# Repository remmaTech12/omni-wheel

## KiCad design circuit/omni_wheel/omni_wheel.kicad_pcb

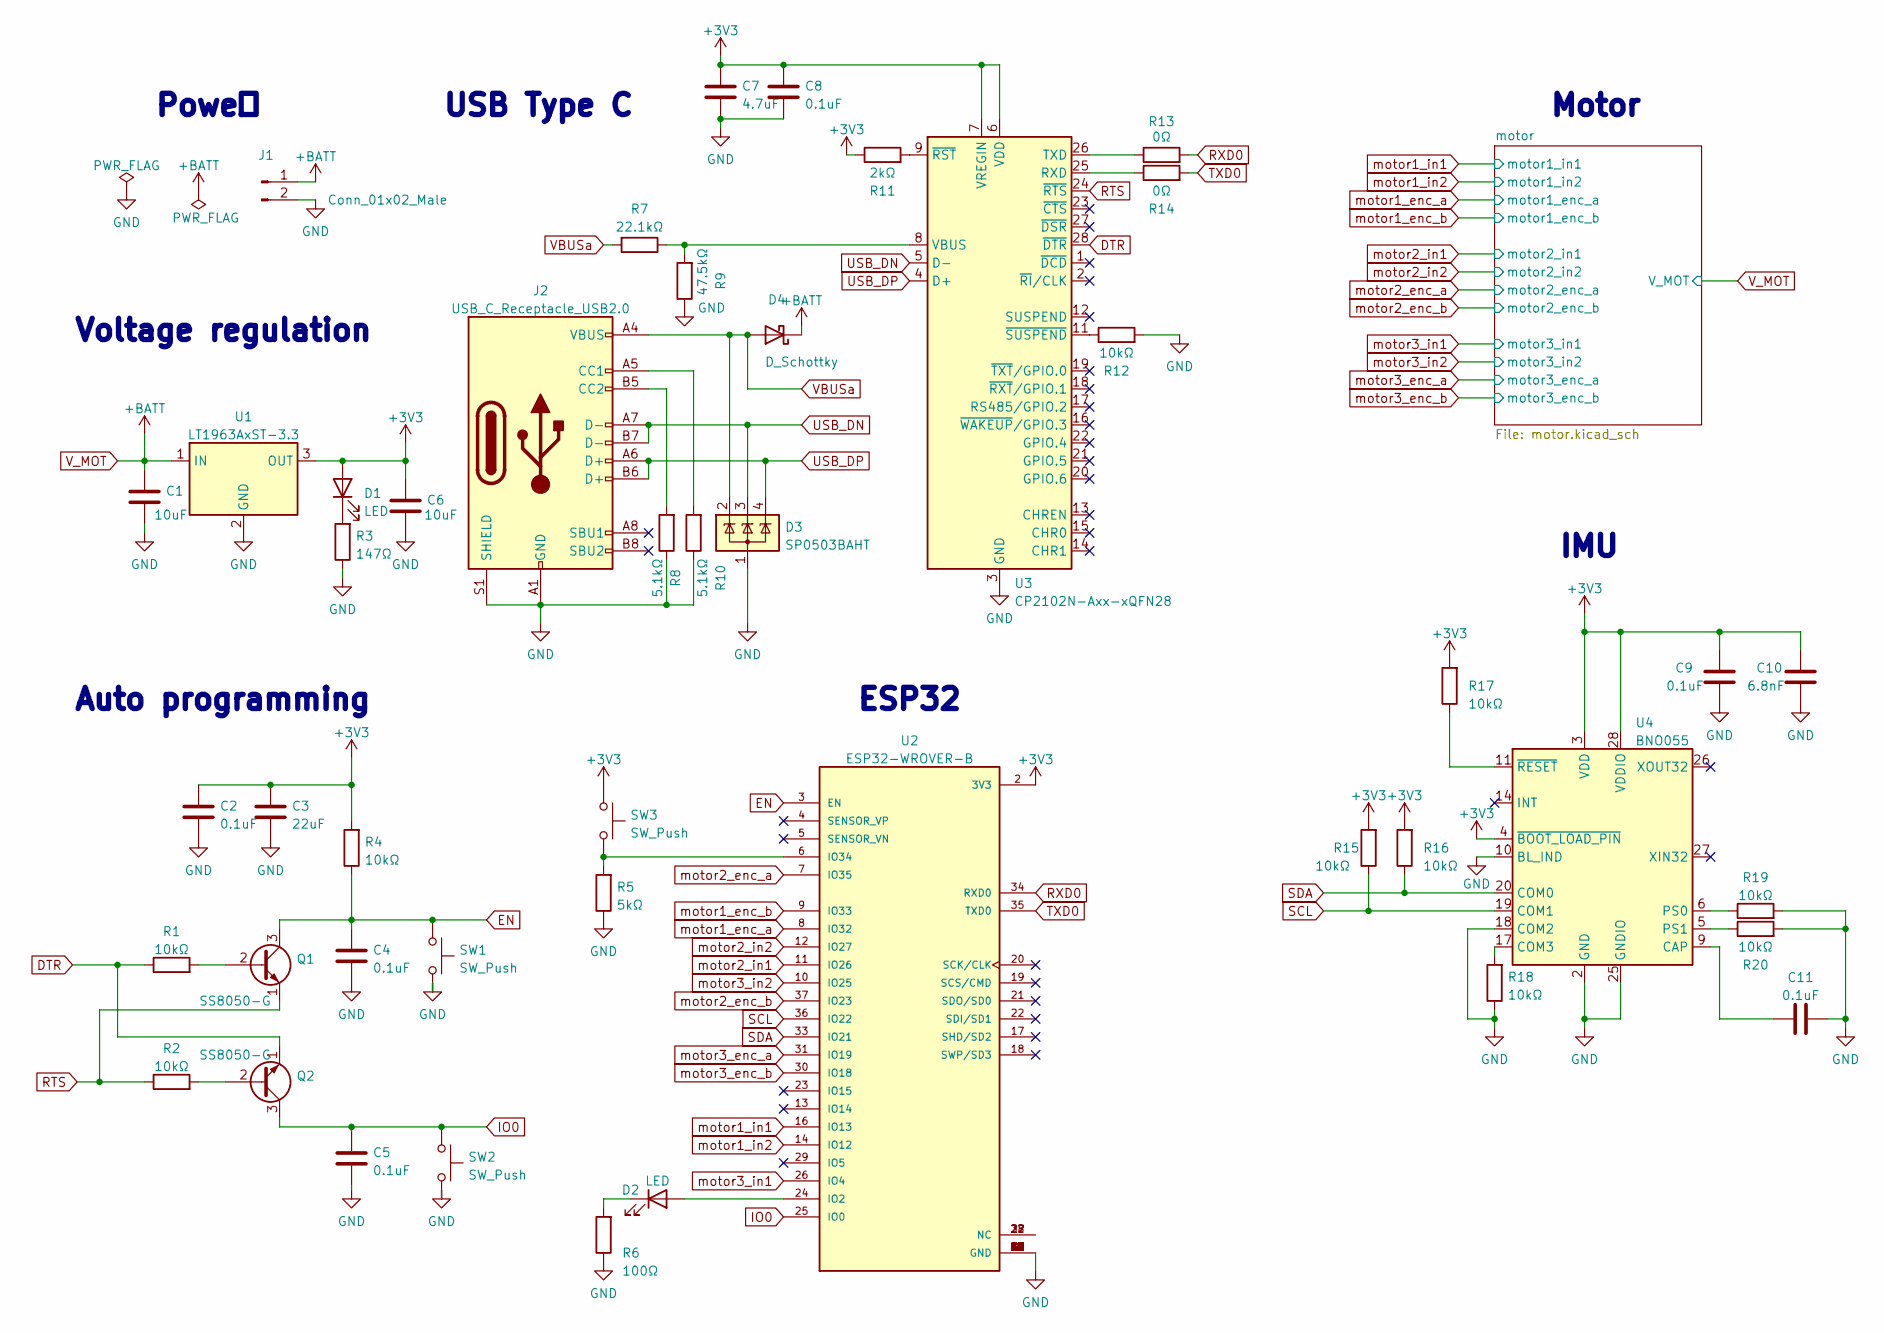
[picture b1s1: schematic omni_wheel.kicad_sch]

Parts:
C1, C6: 10uF; C_0603_1608Metric
C2, C4, C5, C8, C9, C11: 0.1uF; C_0603_1608Metric
C3: 22uF; C_0603_1608Metric
C7: 4.7uF; C_0603_1608Metric
C10: 6.8nF; C_0603_1608Metric
D1, D2: LED; D_0603_1608Metric
D3: SP0503BAHT; SOT-143
D4: D_Schottky; D_0603_1608Metric
J1: Conn_01x02_Male; PinSocket_1x02_P2.54mm_Vertical
J2: USB_C_Receptacle_USB2.0; USB_C_Receptacle_Amphenol_12401610E4-2A
Q1, Q2: SS8050-G; SOT-23
R1, R2, R4, R12, R15, R16, R17, R18, R19, R20: 10kΩ; R_0603_1608Metric
R3: 147Ω; R_0603_1608Metric
R5: 5kΩ; R_0603_1608Metric
R6: 100Ω; R_0603_1608Metric
R7: 22.1kΩ; R_0603_1608Metric
R8, R10: 5.1kΩ; R_0603_1608Metric
R9: 47.5kΩ; R_0603_1608Metric
R11: 2kΩ; R_0603_1608Metric
R13, R14: 0Ω; R_0603_1608Metric
SW1, SW2: SW_Push; SW_Push_1P1T_NO_CK_KMR2
SW3: SW_Push; SW_Push_1P1T_NO_6x6mm_H9.5mm
U1: LT1963AxST-3.3; SOT-223-3_TabPin2
U2: ESP32-WROVER-B; MODULE_ESP32-WROVER-B; PARTREV v1.6
U3: CP2102N-Axx-xQFN28; QFN-28-1EP_5x5mm_P0.5mm_EP3.35x3.35mm
U4: BNO055; LGA-28_5.2x3.8mm_P0.5mm

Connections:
+3V3: C2.1, C3.1, C6.1, C7.1, C8.1, C9.2, C10.2, D1.2 (A), R4.2, R11.1, R15.2, R16.2, R17.2, SW3.1, U1.3 (OUT), U2.2 (3V3), U3.6 (VDD), U3.7 (VREGIN), U4.3 (VDD), U4.4 (~BOOT_LOAD_PIN), U4.28 (VDDIO); also elsewhere on the board
DTR: Q2.1 (E), R1.1, U3.28 (~DTR)
EN: C4.1, Q1.3 (C), R4.1, SW1.1, U2.3 (EN)
GND: C1.2, C2.2, C3.2, C4.2, C5.2, C6.2, C7.2, C8.2, C9.1, C10.1, C11.2, D3.1 (A), J1.2, J2.A1 (GND), J2.A12 (GND), J2.B1 (GND), J2.B12 (GND), J2.S1 (SHIELD), R3.1, R5.1, R6.1, R8.1, R9.1, R10.1, R12.2, R18.1, R19.2, R20.2, SW1.2, SW2.2, U1.2 (GND), U2.1 (GND), U2.15 (GND), U2.38 (GND), U2.39 (GND), U2.40 (GND), U2.41 (GND), U2.42 (GND), U2.43 (GND), U2.44 (GND), U2.45 (GND), U2.46 (GND), U2.47 (GND), U2.48 (GND), U2.49 (GND), U2.50 (GND), U2.51 (GND), U2.52 (GND), U2.53 (GND), U2.54 (GND), U2.55 (GND), U2.56 (GND), U2.57 (GND), U2.58 (GND), U2.59 (GND), U3.3 (GND), U3.29 (GND), U4.2 (GND), U4.10 (BL_IND), U4.15 (GNDIO), U4.16 (GNDIO), U4.18 (COM2), U4.25 (GNDIO); also elsewhere on the board
IO0: C5.1, Q2.3 (C), SW2.1, U2.25 (IO0)
unnamed: C11.1, U4.9 (CAP)
unnamed: D1.1 (K), R3.2
unnamed: D2.1 (K), R6.2
unnamed: D2.2 (A), U2.24 (IO2)
unnamed: J2.A5 (CC1), R10.2
unnamed: J2.B5 (CC2), R8.2
unnamed: Q1.2 (B), R1.2
unnamed: Q2.2 (B), R2.2
unnamed: R5.2, SW3.2, U2.6 (IO34)
unnamed: R7.1, R9.2, U3.8 (VBUS)
unnamed: R11.2, U3.9 (~RST)
unnamed: R12.1, U3.11 (~SUSPEND)
unnamed: R13.1, U3.26 (TXD)
unnamed: R14.1, U3.25 (RXD)
unnamed: R17.1, U4.11 (~RESET)
unnamed: R18.2, U4.17 (COM3)
unnamed: R19.1, U4.6 (PS0)
unnamed: R20.1, U4.5 (PS1)
unnamed: U2.27 (NC), U2.28 (NC), U2.32 (NC)
RTS: Q1.1 (E), R2.1, U3.24 (~RTS)
RXD0: R13.2, U2.34 (RXD0)
SCL: R15.1, U2.36 (IO22), U4.19 (COM1)
SDA: R16.1, U2.33 (IO21), U4.20 (COM0)
TXD0: R14.2, U2.35 (TXD0)
USB_DN: D3.3 (K), J2.A7 (D-), J2.B7 (D-), U3.5 (D-)
USB_DP: D3.4 (K), J2.A6 (D+), J2.B6 (D+), U3.4 (D+)
VBUSa: D3.2 (K), D4.2 (A), J2.A4 (VBUS), J2.A9 (VBUS), J2.B4 (VBUS), J2.B9 (VBUS), R7.2
V_MOT: C1.1, D4.1 (K), J1.1, U1.1 (IN); also elsewhere on the board
motor1_enc_a: U2.8 (IO32); also elsewhere on the board
motor1_enc_b: U2.9 (IO33); also elsewhere on the board
motor1_in1: U2.16 (IO13); also elsewhere on the board
motor1_in2: U2.14 (IO12); also elsewhere on the board
motor2_enc_a: U2.7 (IO35); also elsewhere on the board
motor2_enc_b: U2.37 (IO23); also elsewhere on the board
motor2_in1: U2.11 (IO26); also elsewhere on the board
motor2_in2: U2.12 (IO27); also elsewhere on the board
motor3_enc_a: U2.31 (IO19); also elsewhere on the board
motor3_enc_b: U2.30 (IO18); also elsewhere on the board
motor3_in1: U2.26 (IO4); also elsewhere on the board
motor3_in2: U2.10 (IO25); also elsewhere on the board

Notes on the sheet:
Motor
Poweｒ
Auto programming
IMU
USB Type C
Voltage regulation
ESP32

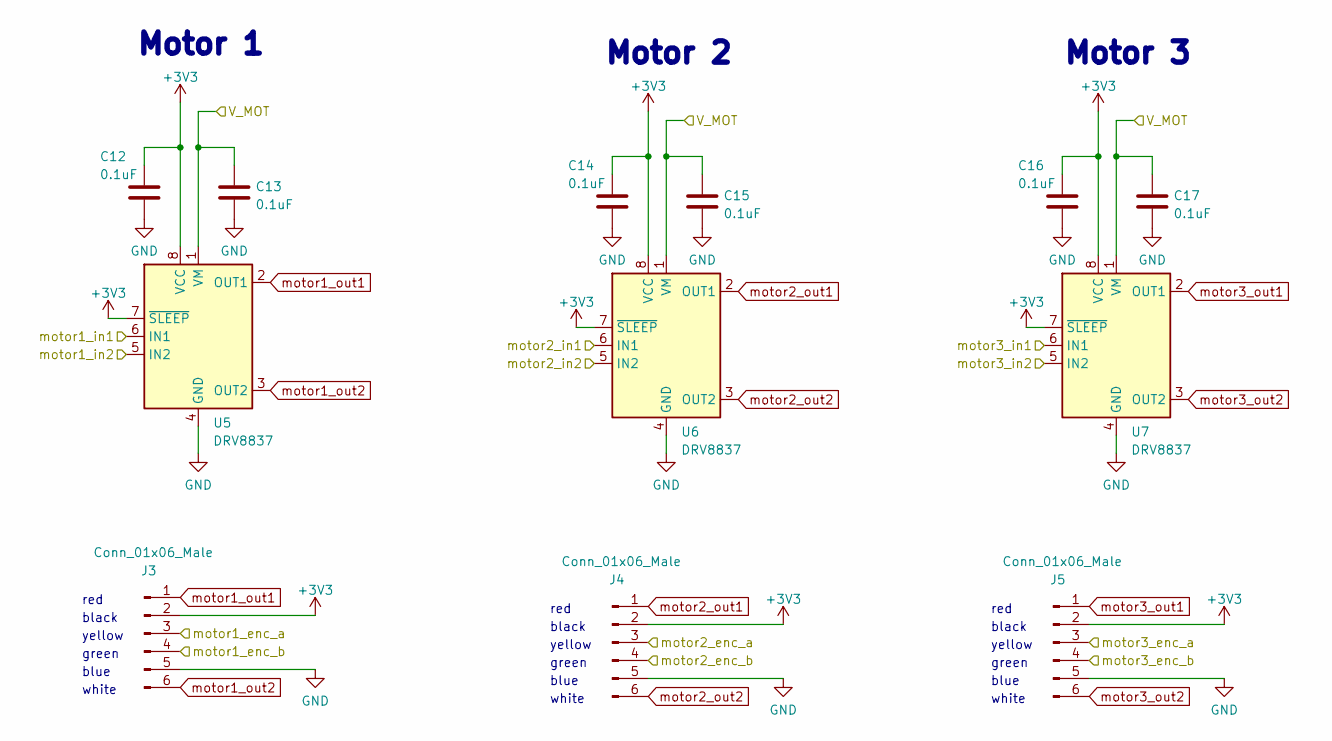
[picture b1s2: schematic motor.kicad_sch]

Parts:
C12, C13, C14, C15, C16, C17: 0.1uF; C_0603_1608Metric
J3, J4, J5: Conn_01x06_Male; PinHeader_1x06_P2.54mm_Vertical
U5, U6, U7: DRV8837; WSON-8-1EP_2x2mm_P0.5mm_EP0.9x1.6mm

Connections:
+3V3: C12.1, C14.1, C16.1, J3.2, J4.2, J5.2, U5.7 (~SLEEP), U5.8 (VCC), U6.7 (~SLEEP), U6.8 (VCC), U7.7 (~SLEEP), U7.8 (VCC); also elsewhere on the board
GND: C12.2, C13.2, C14.2, C15.2, C16.2, C17.2, J3.5, J4.5, J5.5, U5.4 (GND), U5.9 (GND), U6.4 (GND), U6.9 (GND), U7.4 (GND), U7.9 (GND); also elsewhere on the board
V_MOT: C13.1, C15.1, C17.1, U5.1 (VM), U6.1 (VM), U7.1 (VM); also elsewhere on the board
motor1_enc_a: J3.3; also elsewhere on the board
motor1_enc_b: J3.4; also elsewhere on the board
motor1_in1: U5.6 (IN1); also elsewhere on the board
motor1_in2: U5.5 (IN2); also elsewhere on the board
motor1_out1: J3.1, U5.2 (OUT1)
motor1_out2: J3.6, U5.3 (OUT2)
motor2_enc_a: J4.3; also elsewhere on the board
motor2_enc_b: J4.4; also elsewhere on the board
motor2_in1: U6.6 (IN1); also elsewhere on the board
motor2_in2: U6.5 (IN2); also elsewhere on the board
motor2_out1: J4.1, U6.2 (OUT1)
motor2_out2: J4.6, U6.3 (OUT2)
motor3_enc_a: J5.3; also elsewhere on the board
motor3_enc_b: J5.4; also elsewhere on the board
motor3_in1: U7.6 (IN1); also elsewhere on the board
motor3_in2: U7.5 (IN2); also elsewhere on the board
motor3_out1: J5.1, U7.2 (OUT1)
motor3_out2: J5.6, U7.3 (OUT2)

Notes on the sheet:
blue
red
yellow
Motor 3
black
white
green
Motor 2
Motor 1

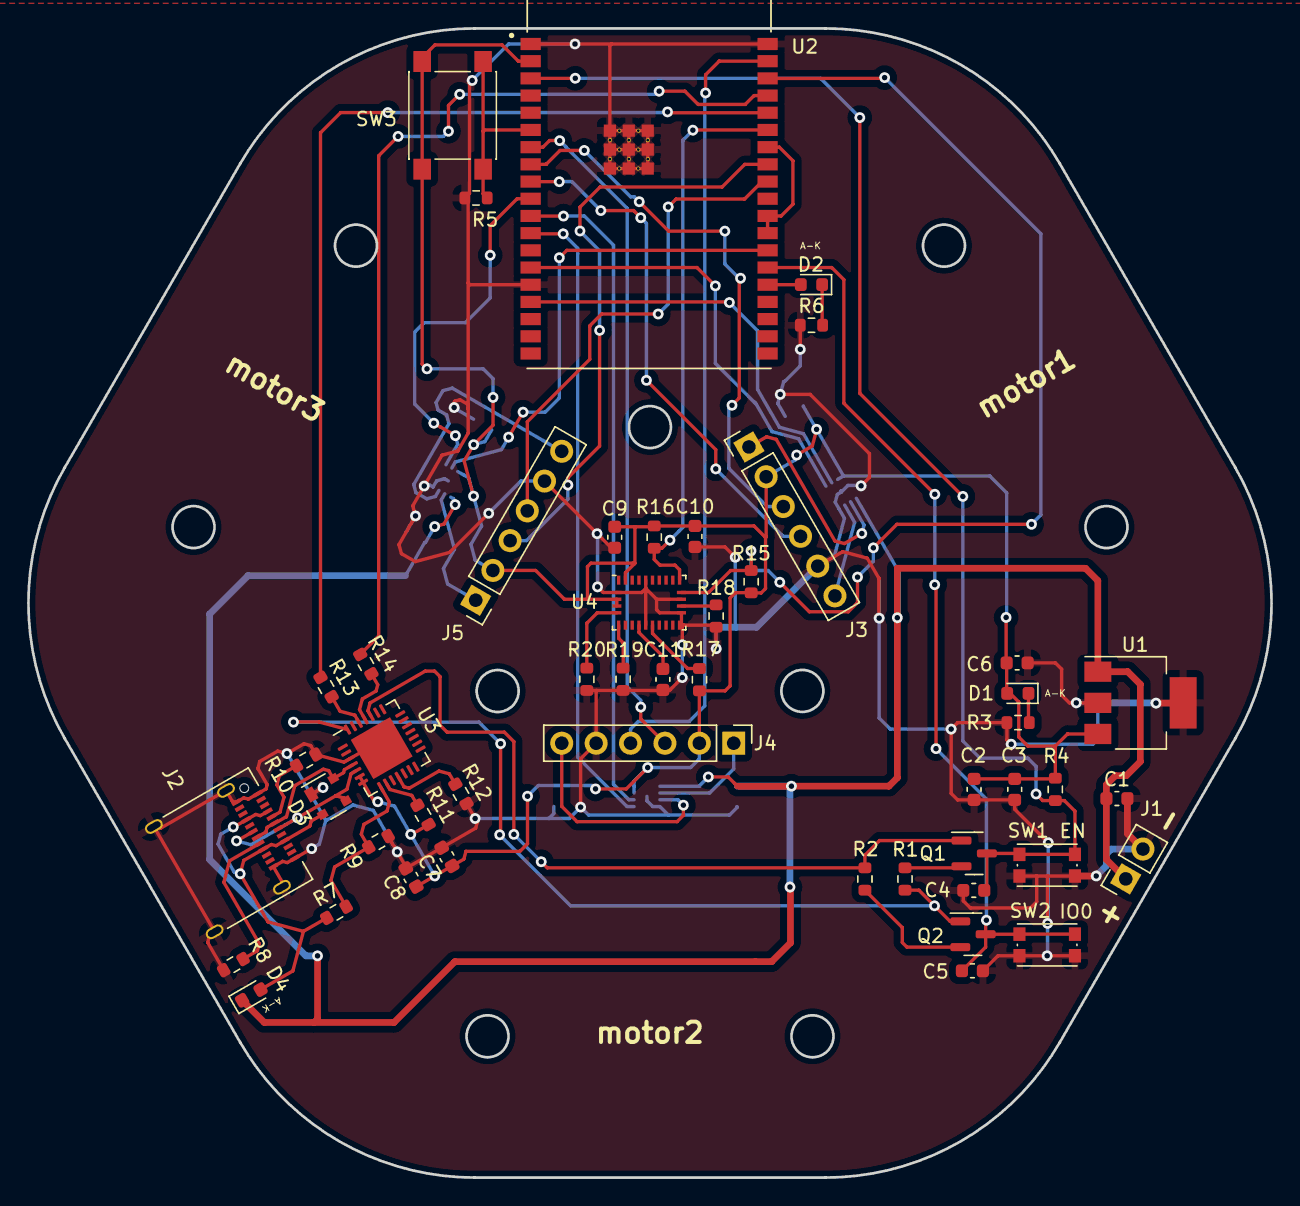
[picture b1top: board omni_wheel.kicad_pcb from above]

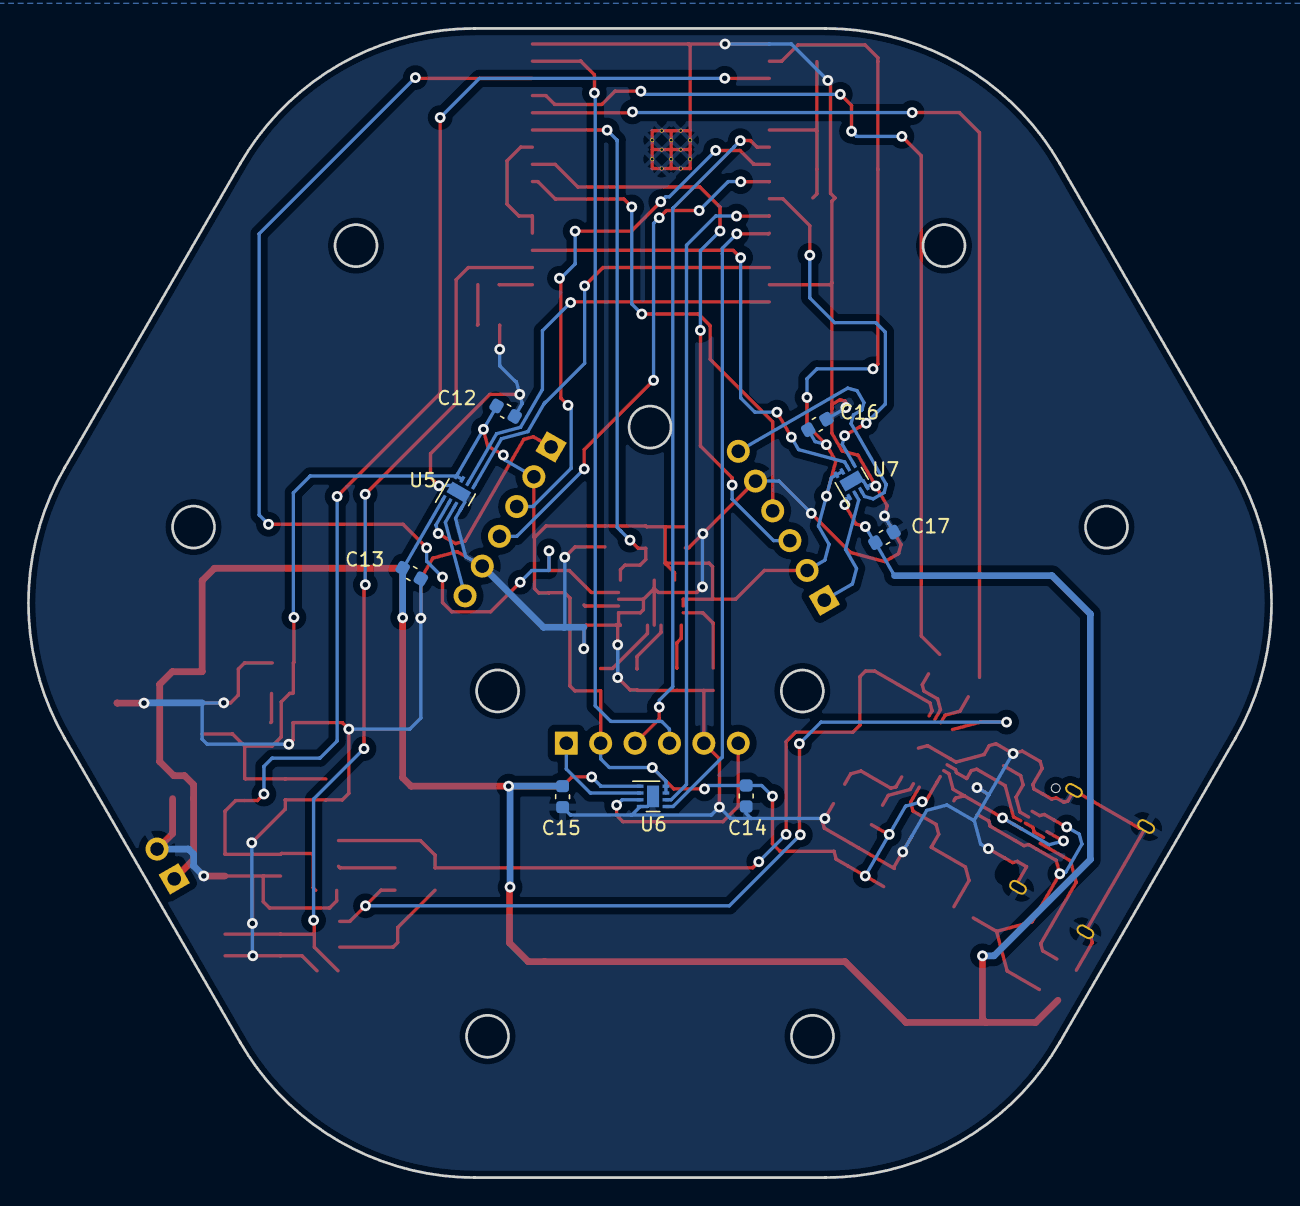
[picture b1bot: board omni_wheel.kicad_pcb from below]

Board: 2 copper layers, 91.8 x 84.9 mm, 58 parts (9 on the bottom side), 51 nets.

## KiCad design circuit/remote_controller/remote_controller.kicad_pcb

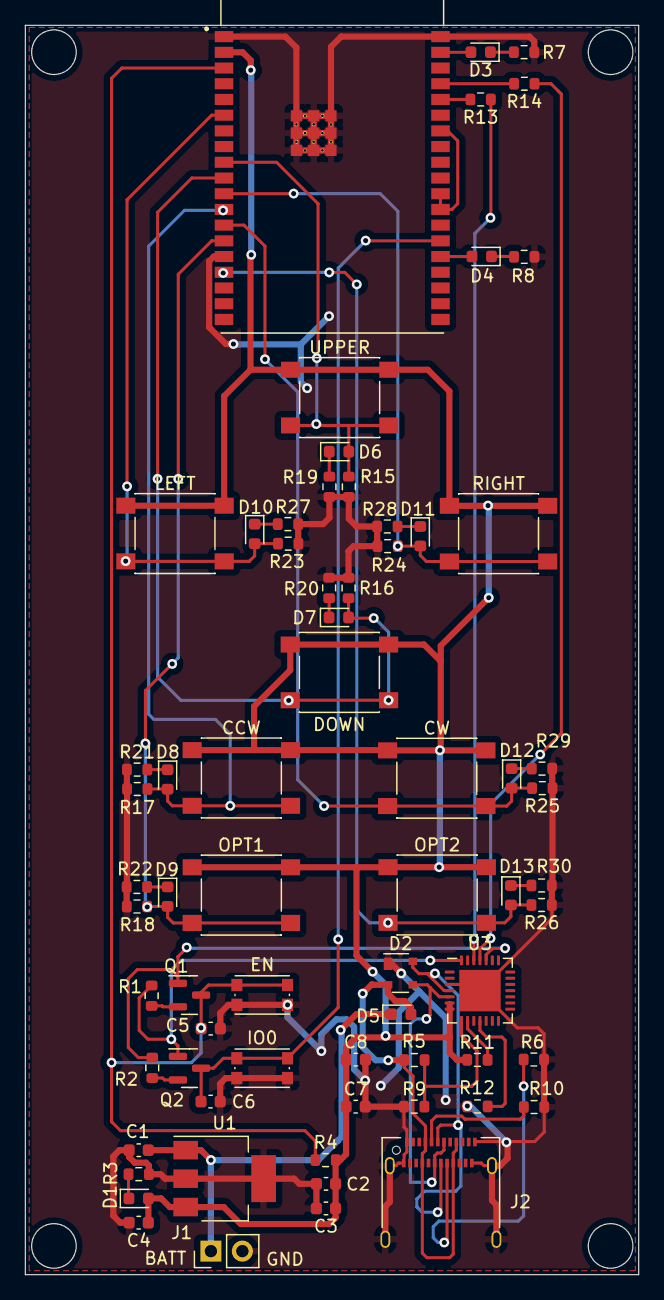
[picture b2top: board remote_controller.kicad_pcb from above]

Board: 2 copper layers, 49.6 x 101.0 mm, 68 parts (0 on the bottom side), 43 nets.

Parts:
C1, C4: 10u; C_0603_1608Metric
C2, C5, C6, C8: 0.1u; C_0603_1608Metric
C3: 22u; C_0603_1608Metric
C7: 4.7u; C_0603_1608Metric
CCW: SW_Push; SW_Push_1P1T_NO_6x6mm_H9.5mm
CW: SW_Push; SW_Push_1P1T_NO_6x6mm_H9.5mm
D1, D3, D4, D6, D7, D8, D9, D10, D11, D12, D13: LED; D_0603_1608Metric
D2: SP0503BAHT; SOT-143
D5: D_Schottky; D_0603_1608Metric
DOWN: SW_Push; SW_Push_1P1T_NO_6x6mm_H9.5mm
EN: SW_Push; SW_Push_1P1T_NO_CK_KMR2
IO0: SW_Push; SW_Push_1P1T_NO_CK_KMR2
J1: Conn_01x02_Male; PinHeader_1x02_P2.54mm_Vertical
J2: USB_C_Receptacle_USB2.0; USB_C_Receptacle_Amphenol_12401610E4-2A
LEFT: SW_Push; SW_Push_1P1T_NO_6x6mm_H9.5mm
OPT1, OPT2: SW_Push; SW_Push_1P1T_NO_6x6mm_H9.5mm
Q1, Q2: SS8050-G; SOT-23
R1, R2, R4, R12: 10k; R_0603_1608Metric
R3: 147; R_0603_1608Metric
R5: 22.1k; R_0603_1608Metric
R6, R10: 5.1k; R_0603_1608Metric
R7, R8, R19, R20, R21, R22, R27, R28, R29, R30: 100; R_0603_1608Metric
R9: 47.5k; R_0603_1608Metric
R11: 2k; R_0603_1608Metric
R13, R14: 0; R_0603_1608Metric
R15, R16, R17, R18, R23, R24, R25, R26: 5k; R_0603_1608Metric
RIGHT: SW_Push; SW_Push_1P1T_NO_6x6mm_H9.5mm
U1: LT1963AxST-3.3; SOT-223-3_TabPin2
U2: ESP32-WROVER-B; MODULE_ESP32-WROVER-B
U3: CP2102N-Axx-xQFN28; QFN-28-1EP_5x5mm_P0.5mm_EP3.35x3.35mm
UPPER: SW_Push; SW_Push_1P1T_NO_6x6mm_H9.5mm

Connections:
+3V3: C2.1, C3.1, C4.1, C7.1, C8.1, CCW.1, CW.1, D1.2 (A), DOWN.1, LEFT.1, OPT1.1, OPT2.1, R4.2, R11.1, RIGHT.1, U1.3 (OUT), U2.2 (3V3), U3.6 (VDD), U3.7 (VREGIN), UPPER.1
+BATT: C1.1, D5.1 (K), J1.1, U1.1 (IN)
DTR: Q2.1 (E), R1.1, U3.28 (~DTR)
EN: C5.1, EN.1, Q1.3 (C), R4.1, U2.3 (EN)
GND: C1.2, C2.2, C3.2, C4.2, C5.2, C6.2, C7.2, C8.2, D2.1 (A), EN.2, IO0.2, J1.2, J2.A1 (GND), J2.A12 (GND), J2.B1 (GND), J2.B12 (GND), J2.S1 (SHIELD), R3.1, R6.1, R7.1, R8.1, R9.1, R10.1, R12.2, R15.1, R16.1, R17.1, R18.1, R19.1, R20.1, R21.1, R22.1, R23.1, R24.1, R25.1, R26.1, R27.1, R28.1, R29.1, R30.1, U1.2 (GND), U2.1 (GND), U2.15 (GND), U2.38 (GND), U2.39 (GND), U2.40 (GND), U2.41 (GND), U2.42 (GND), U2.43 (GND), U2.44 (GND), U2.45 (GND), U2.46 (GND), U2.47 (GND), U2.48 (GND), U2.49 (GND), U2.50 (GND), U2.51 (GND), U2.52 (GND), U2.53 (GND), U2.54 (GND), U2.55 (GND), U2.56 (GND), U2.57 (GND), U2.58 (GND), U2.59 (GND), U3.3 (GND), U3.29 (GND)
IO0: C6.1, IO0.1, Q2.3 (C), U2.25 (IO0)
unnamed: D1.1 (K), R3.2
unnamed: D3.1 (K), R7.2
unnamed: D3.2 (A), U2.37 (IO23)
unnamed: D4.1 (K), R8.2
unnamed: D4.2 (A), U2.24 (IO2)
unnamed: D6.1 (K), R19.2
unnamed: D7.1 (K), R20.2
unnamed: D8.1 (K), R21.2
unnamed: D9.1 (K), R22.2
unnamed: D10.1 (K), R27.2
unnamed: D11.1 (K), R28.2
unnamed: D12.1 (K), R29.2
unnamed: D13.1 (K), R30.2
unnamed: J2.A5 (CC1), R10.2
unnamed: J2.B5 (CC2), R6.2
unnamed: Q1.2 (B), R1.2
unnamed: Q2.2 (B), R2.2
unnamed: R5.1, R9.2, U3.8 (VBUS)
unnamed: R11.2, U3.9 (~RST)
unnamed: R12.1, U3.11 (~SUSPEND)
unnamed: R13.1, U3.26 (TXD)
unnamed: R14.1, U3.25 (RXD)
unnamed: U2.27 (NC), U2.28 (NC), U2.32 (NC)
RTS: Q1.1 (E), R2.1, U3.24 (~RTS)
RXD0: R13.2, U2.34 (RXD0)
TXD0: R14.2, U2.35 (TXD0)
USB_DN: D2.3 (K), J2.A7 (D-), J2.B7 (D-), U3.5 (D-)
USB_DP: D2.4 (K), J2.A6 (D+), J2.B6 (D+), U3.4 (D+)
VBUSa: D2.2 (K), D5.2 (A), J2.A4 (VBUS), J2.A9 (VBUS), J2.B4 (VBUS), J2.B9 (VBUS), R5.2
ccw switch: CCW.2, D8.2 (A), R17.2, U2.12 (IO27)
cw switch: CW.2, D12.2 (A), R25.2, U2.13 (IO14)
down switch: D7.2 (A), DOWN.2, R16.2, U2.10 (IO25)
left switch: D10.2 (A), LEFT.2, R23.2, U2.6 (IO34)
option 1 switch: D9.2 (A), OPT1.2, R18.2, U2.14 (IO12)
option 2 switch: D13.2 (A), OPT2.2, R26.2, U2.16 (IO13)
right switch: D11.2 (A), R24.2, RIGHT.2, U2.11 (IO26)
upper switch: D6.2 (A), R15.2, U2.9 (IO33), UPPER.2

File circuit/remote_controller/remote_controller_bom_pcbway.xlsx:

|  |  | Remote controller BOM
Item # | *Designator | *Qty | Manufacturer | *Mfg Part # | Value | Description / Value | *Package/Footprint | Type | Purchase Link | Your Instructions / Notes
1 | C1, C4, | 2 | KYOCERA AVX | 0603YD106MAT2A | 10uF | Unpolarized capacitor | 0603 inch | SMD | https://www.mouser.jp/ProductDetail/KYOCERA-AVX/0603YD106MAT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
2 | C2, C5, C6, C8, | 4 | KEMET | C0603C104K1RACTU | 0.1uF | Unpolarized capacitor | 0603 inch | SMD | https://www.mouser.jp/ProductDetail/KEMET/C0603C104K1RACTU?q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
3 | C3, | 1 | KYOCERA AVX | KAF15BR71E224KT | 22uF | Unpolarized capacitor | 0603 inch | SMD | https://www.mouser.jp/ProductDetail/KYOCERA-AVX/KAF15BR71E22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
4 | C7, | 1 | KEMET | C0603C475K8PACTU | 4.7uF | Unpolarized capacitor | 0603 inch | SMD | https://www.mouser.jp/ProductDetail/KEMET/C0603C475K8PACTU?q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
5 | D1, D3, D4, D6, D7, D8, D9, D10, D11, D12, D13, | 11 | Bivar | SM0603UBWC | LED | Light emitting diode | 0603 inch | SMD | https://www.mouser.jp/ProductDetail/Bivar/SM0603UBWC?qs=hWDd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
6 | D2, | 1 | Littelfuse | SP0503BAHTG | SP0503BAHT | TVS Diode Array, 5.5V Standoff, 3 Channels SOT-143 package | SOT-143 | SMD | https://www.mouser.jp/ProductDetail/Littelfuse/SP0503BAHTG?q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
7 | D5, | 1 | Bourns | CD0603-B0340R | D_Schottky | Schottky diode | 0603 inch | SMD | https://www.mouser.jp/ProductDetail/Bourns/CD0603-B0340R?qs=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
8 | J1, | 1 |  |  | Male connector | Generic connector, single row, 01x02, script generated | 1x02_P2.54mm | THT |  | No need to mount this part on the board
9 | J2, | 1 | Amphenol Commercial Products | 12401610E4#2A | USB_C_Receptacle_USB2.0 | USB 2.0-only Type-C Receptacle connector | USB_C_Receptacle | SMD | https://www.mouser.jp/ProductDetail/Amphenol-Commercial-Prod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
10 | Q1, Q2, | 2 | Comchip Technology | SS8050-G | SS8050-G | Low Voltage High Current NPN Transistor | SOT-23 | SMD | https://www.mouser.jp/ProductDetail/Comchip-Technology/SS805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
11 | R1, R2, R4, R12, | 4 | Vishay / Beyschlag | MCT0603MG1002BP500 | 10kΩ | Resistor | 0603 inch | SMD | https://www.mouser.jp/ProductDetail/Vishay-Beyschlag/MCT0603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
12 | R3, | 1 | Vishay / Beyschlag | MCT06030C1470FP500 | 147Ω | Resistor | 0603 inch | SMD | https://www.mouser.jp/ProductDetail/Vishay-Beyschlag/MCT0603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
13 | R5, | 1 | YAGEO | RT0603BRB0722K1L | 22.1kΩ | Resistor | 0603 inch | SMD | https://www.mouser.jp/ProductDetail/YAGEO/RT0603BRB0722K1L?q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
14 | R6, R10, | 2 | Vishay / Dale | RCS06035K10FKEA | 5.1kΩ | Resistor | 0603 inch | SMD | https://www.mouser.jp/ProductDetail/Vishay-Dale/RCS06035K10F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
15 | R7, R8, R19, R20, R21, R22, R27, R28, R29, R30, | 10 | Littelfuse | 0603L001/60YR | 100Ω | Resistor | 0603 inch | SMD | https://www.mouser.jp/ProductDetail/Littelfuse/0603L001-60YR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
16 | R9, | 1 | Vishay / Dale | TNPW060347K5BEEA | 47.5kΩ | Resistor | 0603 inch | SMD | https://www.mouser.jp/ProductDetail/Vishay-Dale/TNPW060347K5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
17 | R11, | 1 | Vishay / BC Components | NTCS0603E3202GLT | 2kΩ | Resistor | 0603 inch | SMD | https://www.mouser.jp/ProductDetail/Vishay-BC-Components/NTC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
18 | R13, R14, | 2 | Vishay / Beyschlag | MCT0603HZ0000ZP500 | 0Ω | Resistor | 0603 inch | SMD | https://www.mouser.jp/ProductDetail/Vishay-Beyschlag/MCT0603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
19 | R15, R16, R17, R18, R23 R24, R25, R26, | 8 | Vishay / BC Components | NTCS0603E3502FLT | 5kΩ | Resistor | 0603 inch | SMD | https://www.mouser.jp/ProductDetail/Vishay-BC-Components/NTC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
20 | SW1, SW2, | 2 | C&K | KMR231NGLFS | SW_Push | Push button switch, generic, two pins | KMR2 | SMD | https://www.mouser.jp/ProductDetail/CK/KMR231NGLFS?qs=sb%252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
21 | SW3, SW4, SW5, SW6, SW7, SW8, SW9, SW10, | 8 | Diptronics | DTSM-65N-V-B | SW_Push | Push button switch, generic, two pins | 6x6mm_H9.5mm | SMD | https://www.mouser.jp/ProductDetail/Diptronics/DTSM-65N-V-B?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
22 | U1, | 1 | Analog Devices | LT1963AEST-3.3#PBF | LT1963AxST-3.3 | 3.3V, 1.5A, Low Noise, Fast Transient Response LDO Regulator, SOT-223 | SOT-223-3 | SMD | https://www.mouser.jp/ProductDetail/Analog-Devices/LT1963AES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
23 | U2, | 1 | Espressif Systems | ESP32-WROVER-B-N8R8 | ESP32-WROVER-B | ESP32-WROVER-B | ESP32-WROVER-B | SMD | https://www.digikey.jp/ja/products/detail/espressif-systems/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 | Should have 技適 mark to use in Japan.
24 | U3, | 1 | Silicon Labs | CP2102N-A02-GQFN28 | CP2102N-Axx-xQFN28 | USB to UART master bridge, QFN-28 | Package_DFN_QFN: QFN-28-1EP 5x5mm_P0.5mm_EP3.35x3.35mm | SMD | https://www.mouser.jp/ProductDetail/Silicon-Labs/CP2102N-A02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

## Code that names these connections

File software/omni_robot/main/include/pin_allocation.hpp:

#define MOTOR1_ENC_A_PIN 32
#define MOTOR1_ENC_B_PIN 33
#define MOTOR1_IN1_PIN 13
#define MOTOR1_IN2_PIN 12

#define MOTOR2_ENC_A_PIN 35
#define MOTOR2_ENC_B_PIN 23
#define MOTOR2_IN1_PIN 26
#define MOTOR2_IN2_PIN 27

#define MOTOR3_ENC_A_PIN 19
#define MOTOR3_ENC_B_PIN 18
#define MOTOR3_IN1_PIN 4
#define MOTOR3_IN2_PIN 25

#define LED_PIN 2
#define SW_PIN 34

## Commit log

2021-11-01 initial commit: dynamics modelling
2021-11-13 Refactoring has been done.
2021-12-19 Simulation and animation are added.
2021-12-25 Other simulations are added.
2021-12-26 fps for saving a gif is designated.
2023-08-05 add velocity calculation.
2024-03-29 Add remote controller circuit.
2024-03-29 Added csv file.
2024-03-31 Remove backup files.
2024-03-31 Apply the circuit design; add holes at each corner.
2024-03-31 Add circuit diagram pdf and parts list.
2024-05-18 as of 20240518
2024-05-18 add centroids and gerber files.
2024-05-18 add plot
2024-05-18 update centroids file.
2024-05-19 temporary commit for arduino software
2024-05-26 messy code; but done classification of motor.
2024-05-26 refactor for callback registration.
2024-05-26 overall motor.hpp refactoring done.
2024-05-26 utilize the array for motor instance.
2024-05-26 control 3 motors independently.
2024-05-26 separate PID instances.
2024-06-08 add remote controller code.
2024-06-08 add finalized BOM.
2024-06-16 Original code from Akiduki.
2024-07-07 rename bmx055 file.
2024-07-07 add imu and change PINs.
2024-08-10 Modify PIN alias names.
2024-08-11 PIN allocation change: all the motor worked.
2024-08-11 utilize bno sensor.
2024-08-11 add switch.
2024-11-07 update 3d printed parts.
2024-11-07 update remote controller backup files.
2024-11-07 update 3dprint parts data.
2024-11-07 add .gitignore.
2024-11-07 add omni-wheel circuit.
2024-11-07 update .gitignore.
2024-11-07 update inverted pendulum.
2024-12-01 redesign omni-wheel base.
2024-12-01 connect nsleep to high and remove unnecessary switch.
2024-12-01 redesign the PCB: the direction of parts.
2024-12-01 connect nsleep to high and remove unnecessary switch (2/2).
2024-12-01 change the pdf name.
2024-12-01 add csv and xml files.
2024-12-01 add purchase order files.
2024-12-02 modified 3d print part for motor bracket.
2024-12-15 Revised based on review 2024 Dec 7th.
2024-12-20 thicken and add reiforcement material for 3D print parts.
2024-12-26 Make the bracket base thinner.
2024-12-31 rotate motor only when the switch is pressed.
2025-01-01 Communication between robot and remote controller is established.
2025-01-01 refactoring for remote controller and omni-wheel robot.
2025-01-01 add manipulation on remote controller commands.
2025-01-01 fix a bug on the remote controller key bind.
2025-01-01 rm unnecessary file.
2025-01-01 fix bug: motor direction and horizontal movement.
2025-01-17 temporarily messy code: inverted pendulum worked.
2025-01-17 inverted pendulum code refactoring
2025-01-17 separate pin allocation hpp.
2025-01-17 stop motor when command is not coming in NOT inverted_pendulum mode.
2025-01-17 remove unnecessary comment out.
2025-01-17 add util class.
2025-01-17 setup function is tidied up.
2025-01-17 add body_control and tidy up.
2025-01-17 switch inverted pendulum mode or not by pressing button.
2025-01-17 [refactor] button press judgement process
2025-01-17 [refactoring] transfer control mode processing to body_control.
2025-01-17 [refactoring] variable and function name change.
2025-01-17 [refactoring] remove unnecessary space.
2025-01-17 remove unnecessary min command threshold.
2025-01-26 put remote controller submission data in a single directory.
2025-01-26 rename directory
2025-01-26 rename file.
2025-01-26 remove backups.
2025-01-26 add pid for inverted pendulum control.
2025-01-28 add licence.
2025-01-29 disable imu to make it work with connecting to battery.
